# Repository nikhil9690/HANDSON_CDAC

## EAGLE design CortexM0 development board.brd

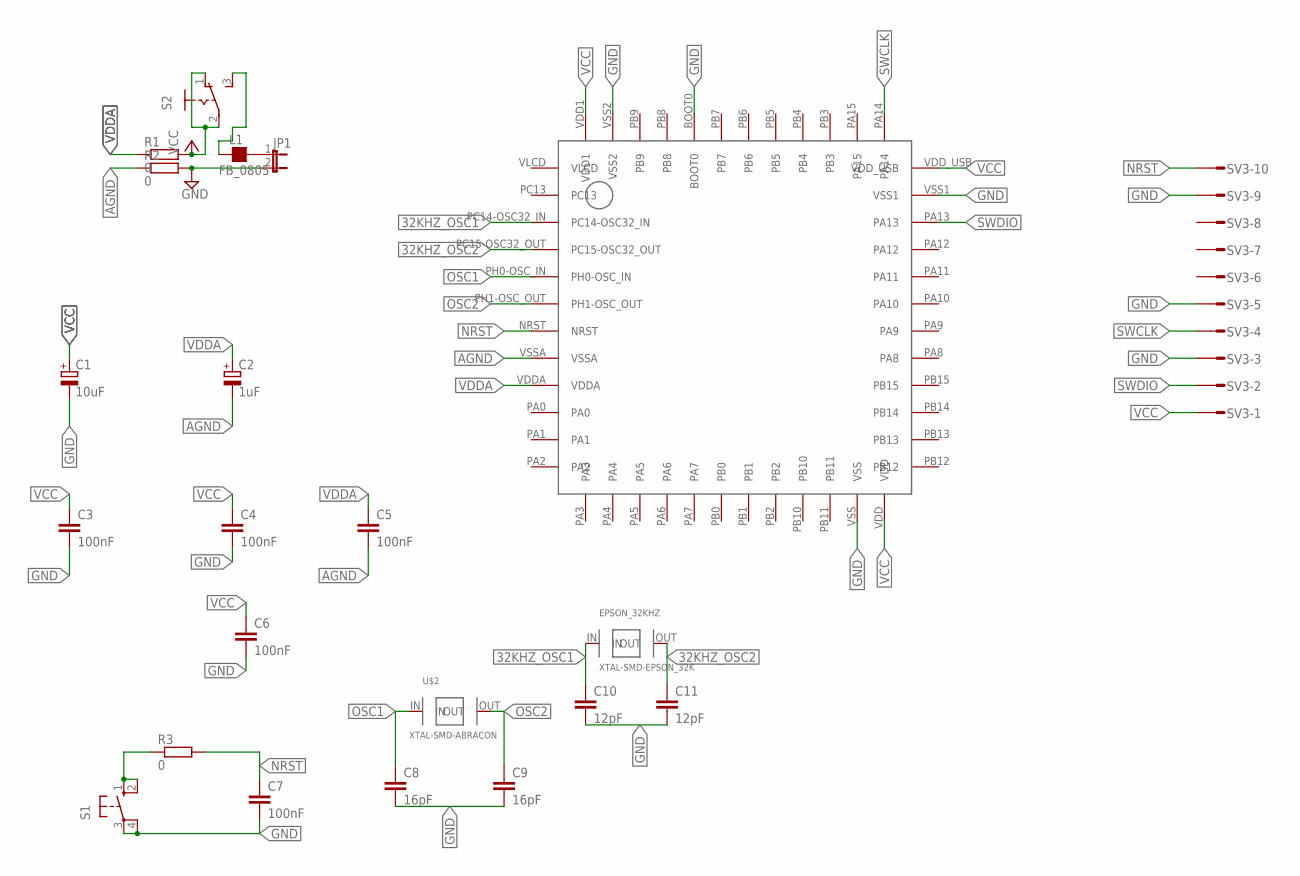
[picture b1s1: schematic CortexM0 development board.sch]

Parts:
C1: 10uF; PANASONIC_B
C2: 1uF; PANASONIC_B
C3, C4, C5, C6, C7: 100nF; C0805
C8, C9: 16pF; C0805
C10, C11: 12pF; C0805
EPSON_32KHZ: XTAL-SMD-EPSON_32K; XTAL-EPSON-FC135R
JP1: JP1E; JP1
L1: FB_0805; L0805
R1, R2, R3: 0; R0805
S1: 10-XX; B3F-10XX
S2: 255SB
SV3: S10P
U$1: STM32L083-LQFP48; LQFP_48
U$2: XTAL-SMD-ABRACON

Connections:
32KHZ_OSC1: C10.1, EPSON_32KHZ.IN, U$1.PC14-OSC32_IN
32KHZ_OSC2: C11.1, EPSON_32KHZ.OUT, U$1.PC15-OSC32_OUT
AGND: C2.-, C5.2, R2.1, U$1.VSSA
GND: C1.-, C3.2, C4.2, C6.2, C7.2, C8.2, C9.2, C10.2, C11.2, JP1.2, R2.2, S1.3, S1.4 (P1), SV3.3, SV3.5, SV3.9, U$1.BOOT0, U$1.VSS, U$1.VSS1, U$1.VSS2
unnamed: JP1.1, L1.2
unnamed: R3.1, S1.1 (S), S1.2 (S1)
unnamed: L1.1, S2.3 (S)
NRST: C7.1, R3.2, SV3.10, U$1.NRST
OSC1: C8.1, U$1.PH0-OSC_IN, U$2.IN
OSC2: C9.1, U$1.PH1-OSC_OUT, U$2.OUT
SWCLK: SV3.4, U$1.PA14
SWDIO: SV3.2, U$1.PA13
VCC: C1.+, C3.1, C4.1, C6.1, R1.2, S2.1 (O), S2.2, SV3.1, U$1.VDD, U$1.VDD1, U$1.VDD_USB
VDDA: C2.+, C5.1, R1.1, U$1.VDDA

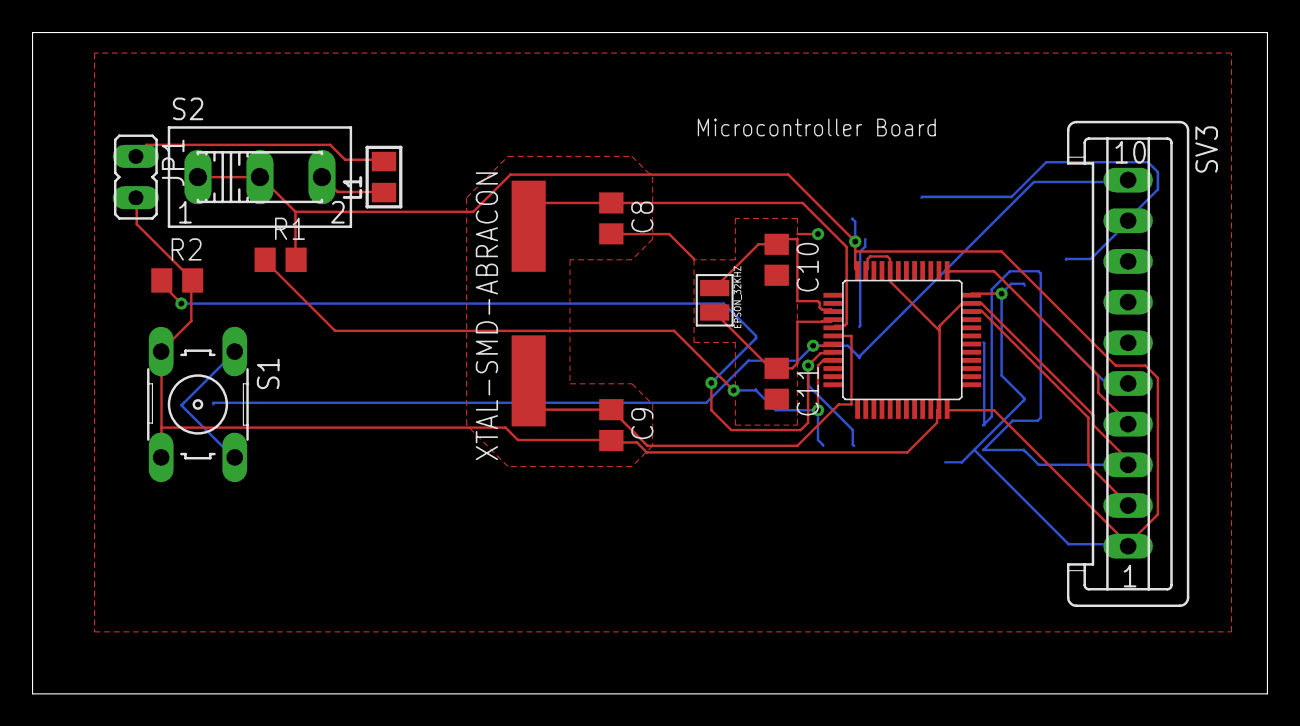
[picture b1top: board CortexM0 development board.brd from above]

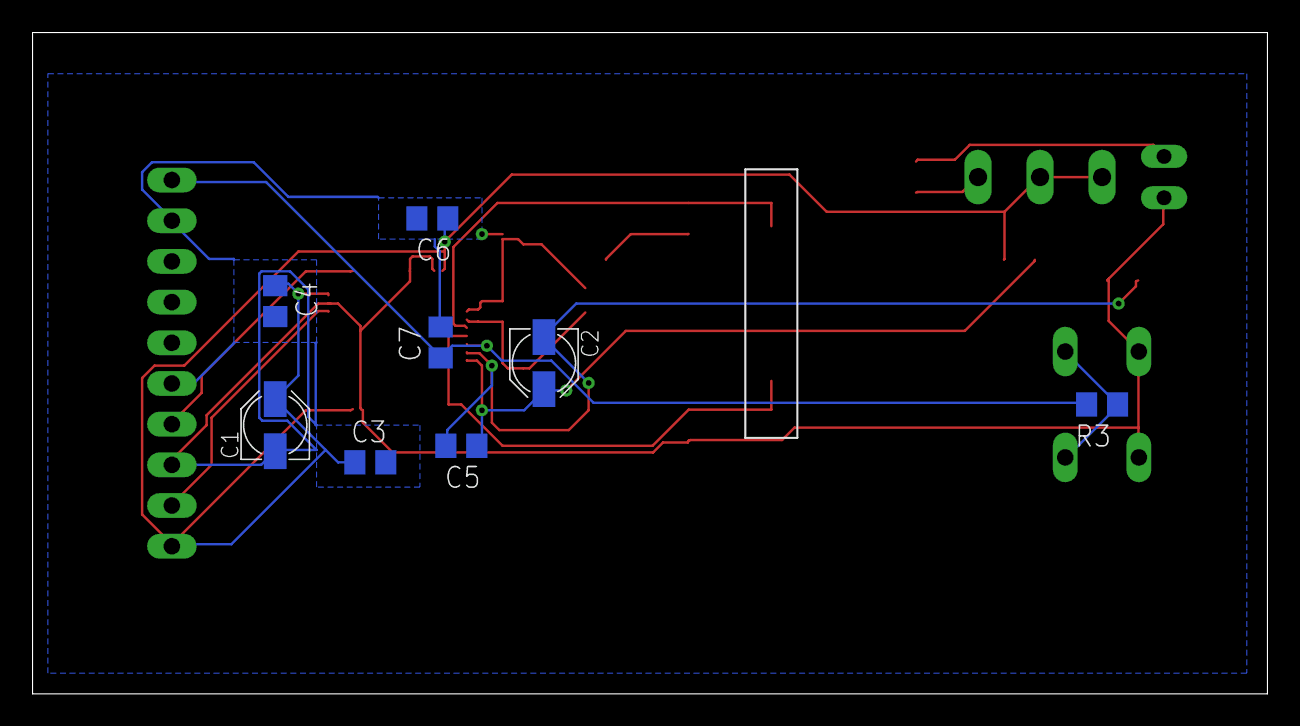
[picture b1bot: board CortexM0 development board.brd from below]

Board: 2 copper layers, 75.9 x 40.6 mm, 22 parts (8 on the bottom side), 14 nets.

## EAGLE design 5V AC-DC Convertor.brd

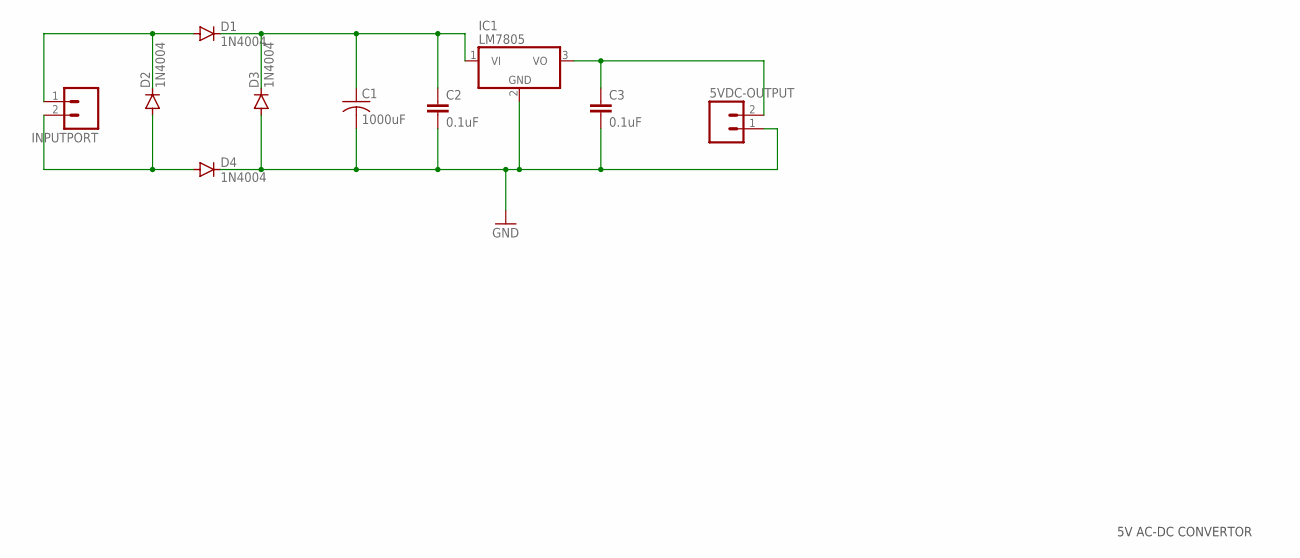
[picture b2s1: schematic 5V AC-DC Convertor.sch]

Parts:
5VDC-OUTPUT: M02; 02P
C1: 1000uF; C025-024X044
C2, C3: 0.1uF; C025-025X050
D1, D2, D3, D4: 1N4004; DO41-10
IC1: LM7805; TO220V
INPUTPORT: M02; 02P

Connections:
GND: 5VDC-OUTPUT.1, C1.2, C2.2, C3.2, D3.A, D4.C, IC1.2 (GND)
unnamed: D1.A, D2.C, INPUTPORT.1
unnamed: D2.A, D4.A, INPUTPORT.2
unnamed: C1.1, C2.1, D1.C, D3.C, IC1.1 (VI)
unnamed: 5VDC-OUTPUT.2, C3.1, IC1.3 (VO)

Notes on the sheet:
5V AC-DC CONVERTOR

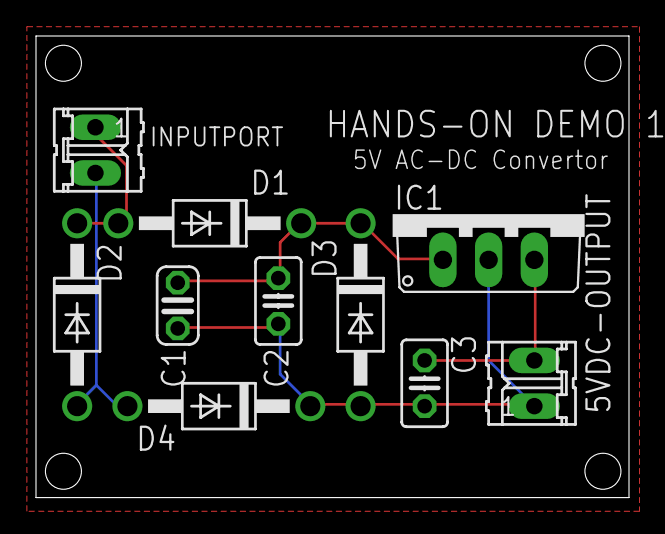
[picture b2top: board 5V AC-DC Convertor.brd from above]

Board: 2 copper layers, 32.9 x 25.6 mm, 10 parts (0 on the bottom side), 5 nets.

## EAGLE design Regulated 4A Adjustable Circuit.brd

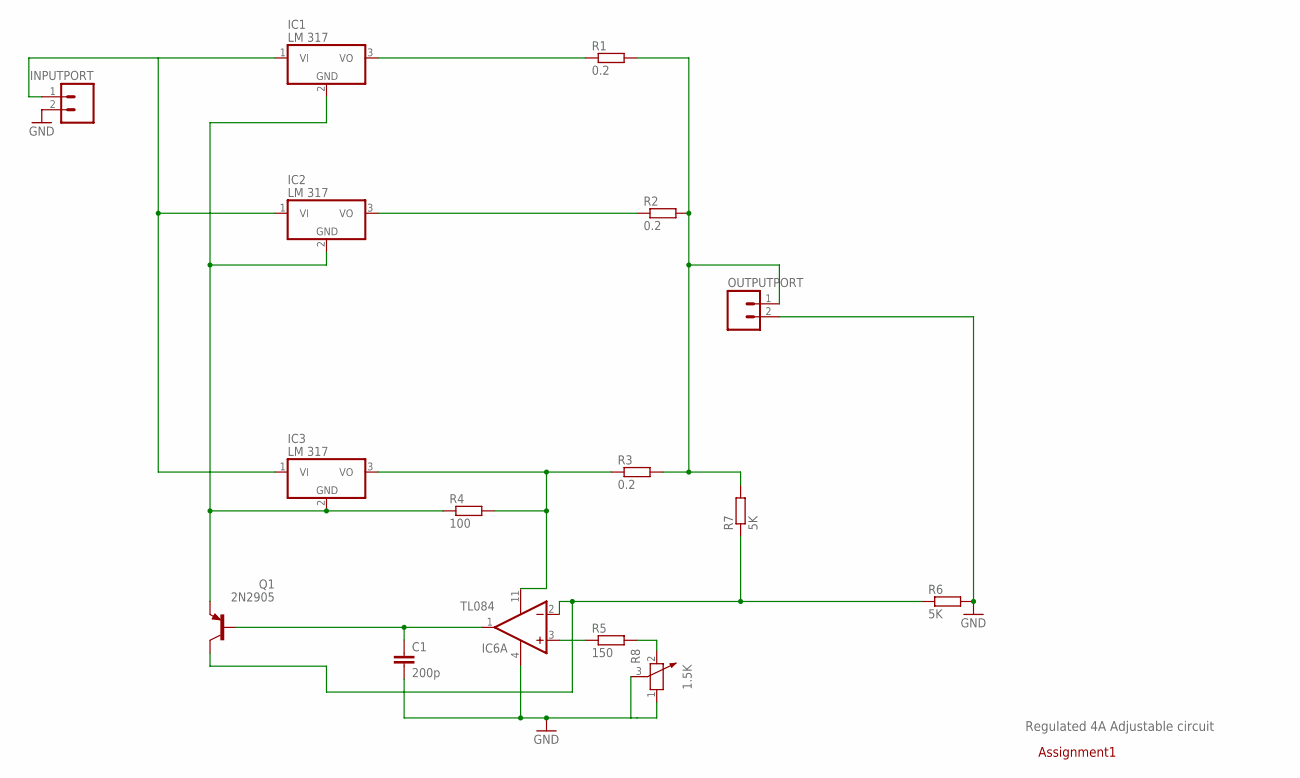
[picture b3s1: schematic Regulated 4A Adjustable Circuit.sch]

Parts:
C1: 200p; C025-025X050
IC1, IC2, IC3: LM 317; TO220V
IC6: TL084; DIL14
Q1: 2N2905; TO39
R1, R2, R3: 0.2; 0207/10
R4: 100; 0207/10
R5: 150; 0207/10
R6, R7: 5K; 0207/10
R8: 1.5K; PT-10
SL1: INPUTPORT; 02P
SL2: OUTPUTPORT; 02P

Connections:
GND: C1.2, IC6.4 (V+), R6.2, R8.1, R8.3, SL1.2, SL2.2
unnamed: IC1.3 (VO), R1.1
unnamed: IC2.3 (VO), R2.1
unnamed: IC3.3 (VO), IC6.11 (V-), R3.1, R4.2
unnamed: R1.2, R2.2, R3.2, R7.2, SL2.1
unnamed: IC6.3 (+IN), R5.1
unnamed: IC6.2 (-IN), Q1.3 (C), R6.1, R7.1
unnamed: R5.2, R8.2
unnamed: IC1.2 (GND), IC2.2 (GND), IC3.2 (GND), Q1.1 (E), R4.1
unnamed: IC1.1 (VI), IC2.1 (VI), IC3.1 (VI), SL1.1
unnamed: C1.1, IC6.1 (OUT), Q1.2 (B)

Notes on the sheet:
Regulated 4A Adjustable circuit
Assignment1

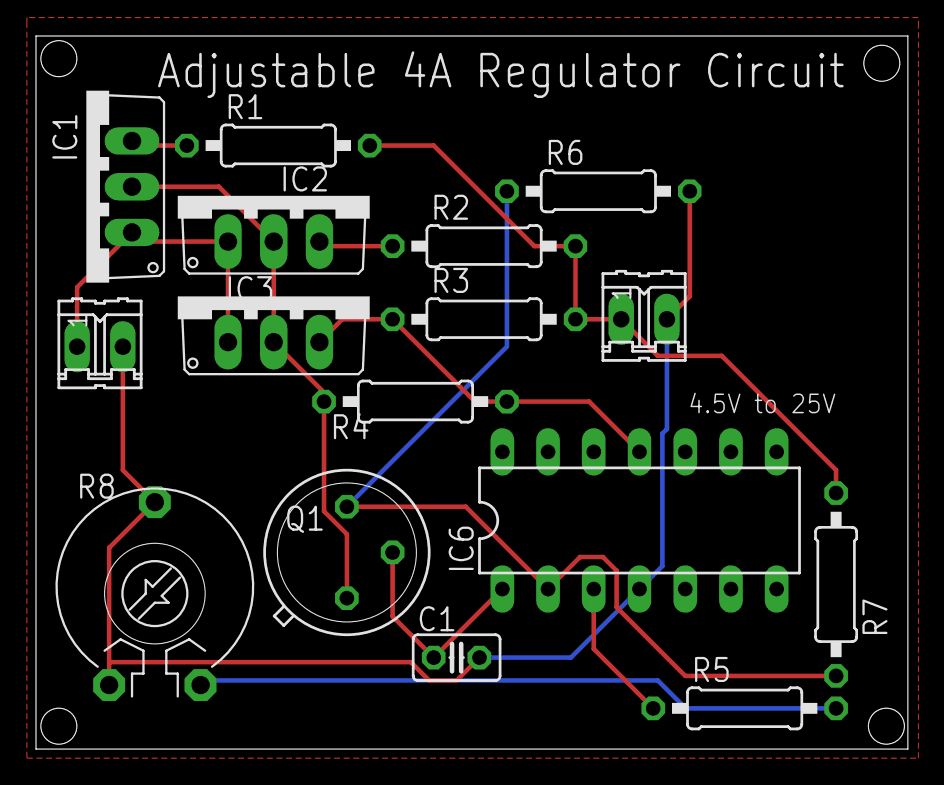
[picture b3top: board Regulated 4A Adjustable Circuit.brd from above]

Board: 2 copper layers, 48.4 x 39.6 mm, 16 parts (0 on the bottom side), 11 nets.

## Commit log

2021-04-29 Add files via upload
    LM35 and RC-master libraries are downloaded from the internet

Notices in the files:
parts and their libraries:
rc-master: Copyright (C) 2007, Bob Starr
